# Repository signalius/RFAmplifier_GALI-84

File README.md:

## GALI-84+ RF Amplifier
* Impedance 50 ohm is calculated for FR4 0.8mm
* Maximum frequency is 6GHz (I tested only to 4GHz)

## LICENSE
GNU General Public License v3.0

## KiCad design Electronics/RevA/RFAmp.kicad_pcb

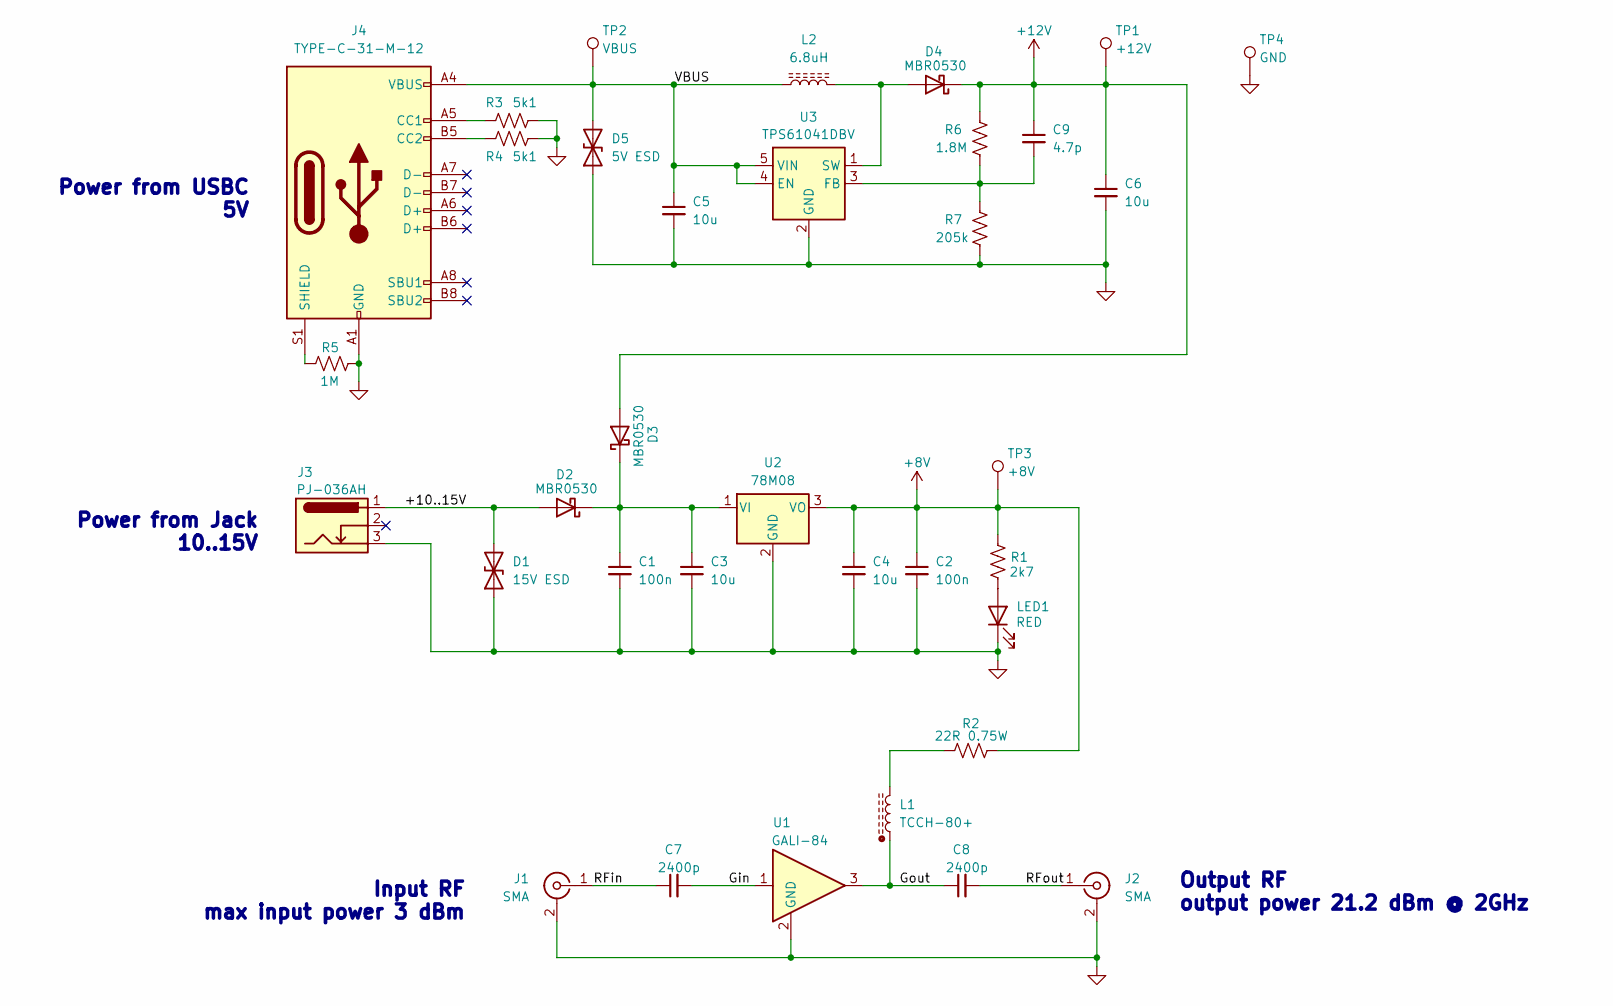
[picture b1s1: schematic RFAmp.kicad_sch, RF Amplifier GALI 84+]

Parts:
C1, C2: 100n; C_0603_1608Metric
C3, C4, C5, C6: 10u; C_1206_3216Metric; MPN GRM31CR71E106KA12L
C7, C8: 2400p; C_0805_2012Metric; MPN GRM2165C1H242JA01D
C9: 4.7p; C_0603_1608Metric; MPN CC0603CPNPO9BN4R7
D1: 15V ESD; D_SOD-323; MPN PESD15VL1BA
D2, D3, D4: MBR0530; D_SOD-123; MPN MBR0530T1G
D5: 5V ESD; D_SOD-323; MPN PESD5V0L1BA,115
J1, J2: SMA; SMA_Amphenol_132289_EdgeMount
J3: PJ-036AH; BarrelJack_CUI_PJ-036AH-SMT_Horizontal; MPN PJ-036AH
J4: TYPE-C-31-M-12; USB_C_Receptacle_HRO_TYPE-C-31-M-12; MPN TYPE-C-31-M-12
L1: TCCH-80+; MPN TCCH-80+
L2: 6.8uH; L_1210_3225Metric_Pad1.42x2.65mm_HandSolder; MPN LQH32MN6R8K23L
LED1: RED; LED_0805_2012Metric; MPN 150080RS75000
R1: 2k7; R_0603_1608Metric
R2: 22R 0.75W; R_1210_3225Metric
R3, R4: 5k1; R_0603_1608Metric
R5: 1M; R_0603_1608Metric
R6: 1.8M; R_0603_1608Metric
R7: 205k; R_0603_1608Metric
TP1: +12V; TestPoint_THTPad_1.5x1.5mm_Drill0.7mm
TP2: VBUS; TestPoint_THTPad_1.5x1.5mm_Drill0.7mm
TP3: +8V; TestPoint_THTPad_1.5x1.5mm_Drill0.7mm
TP4: GND; TestPoint_THTPad_1.5x1.5mm_Drill0.7mm
U1: GALI-84; SOT-89-3; MPN GALI-84
U2: 78M08; TO-252-2; MPN L78M08ABDT
U3: TPS61041DBV; SOT-23-5; MPN TPS61041DBV

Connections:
+8V: C2.1, C4.1, R1.1, R2.2, TP3.1, U2.3 (VO)
+12V: C6.1, C9.1, D3.2 (A), D4.1 (K), R6.1, TP1.1
/+10..15V: D1.2 (A2), D2.2 (A), J3.1
/Gin: C7.2, U1.1
/Gout: C8.1, L1.1, U1.3
/RFin: C7.1, J1.1 (In)
/RFout: C8.2, J2.1 (In)
/VBUS: C5.1, D5.2 (A2), J4.A4 (VBUS), J4.A9 (VBUS), J4.B4 (VBUS), J4.B9 (VBUS), L2.1, TP2.1, U3.4 (EN), U3.5 (VIN)
GND: C1.2, C2.2, C3.2, C4.2, C5.2, C6.2, D1.1 (A1), D5.1 (A1), J1.2 (Ext), J2.2 (Ext), J3.3, J4.A1 (GND), J4.A12 (GND), J4.B1 (GND), J4.B12 (GND), LED1.1 (K), R3.2, R4.2, R5.2, R7.2, TP4.1, U1.2 (GND), U2.2 (GND), U3.2 (GND)
unnamed: C1.1, C3.1, D2.1 (K), D3.1 (K), U2.1 (VI)
unnamed: D4.2 (A), L2.2, U3.1 (SW)
unnamed: J4.A5 (CC1), R3.1
unnamed: J4.B5 (CC2), R4.1
unnamed: J4.S1 (SHIELD), R5.1
unnamed: L1.3, R2.1
unnamed: LED1.2 (A), R1.2
unnamed: C9.2, R6.2, R7.1, U3.3 (FB)

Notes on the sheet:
Input RF max input power 3 dBm
Power from Jack 10..15V
Power from USBC 5V
Output RF output power 21.2 dBm @ 2GHz

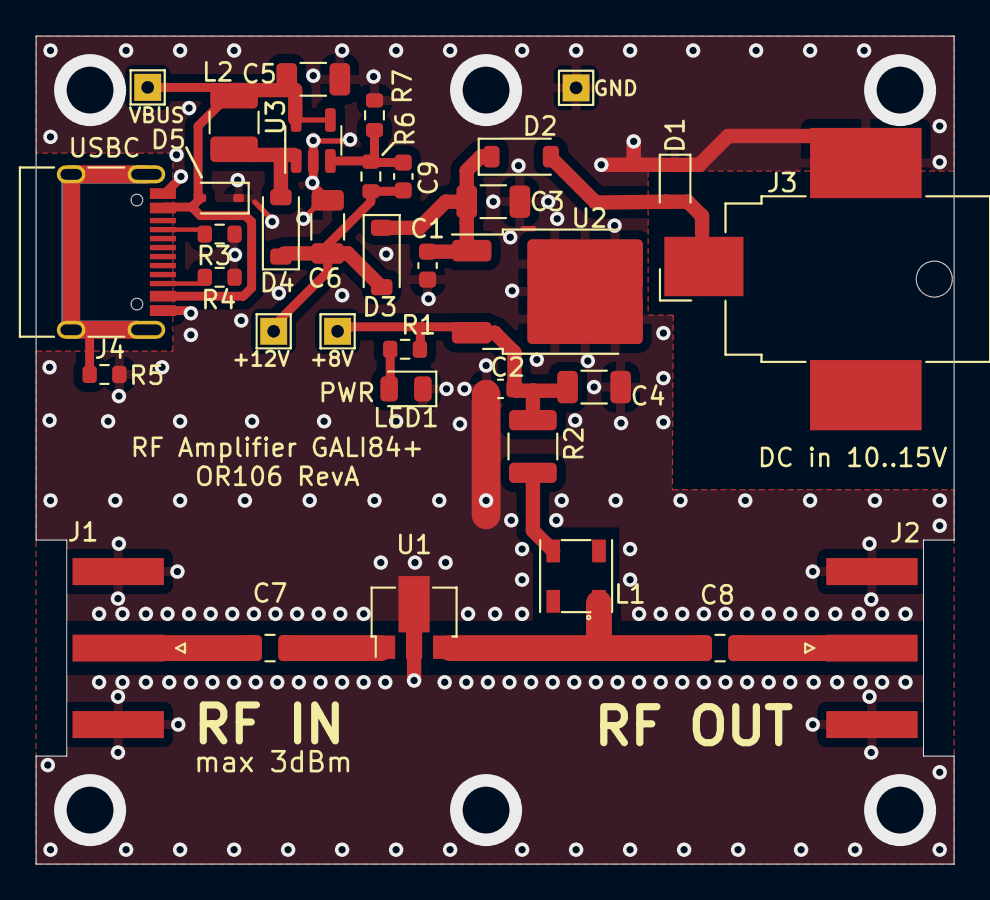
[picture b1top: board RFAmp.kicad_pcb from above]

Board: 2 copper layers, 51.0 x 46.0 mm, 35 parts (0 on the bottom side), 17 nets.

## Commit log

2023-10-02 Initial
2023-10-02 Readme
2023-10-04 Cosmetic
